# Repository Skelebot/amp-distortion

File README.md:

# Micro amp / distortion guitar pedal
Open-source micro amplifier guitar pedal with germanium diode distortion, heavily inspired by [MXR MicroAmp](https://www.jimdunlop.com/mxr-micro-amp/) and [MXR Distortion+](https://www.jimdunlop.com/mxr-distortion/).

## Features:
 - Clean and transparent volume boost with flat frequency response
 - Optional germanium diode signal clipping with a simple ON-ON switch (distortion)
 - True bypass using a 2PDT ON-ON switch
 - Completely un-colored sound, even with distortion on
 - Small board form factor (30mm x 55mm), most THT elements replaced with SMD
 - Smooth type distortion thanks to traditional germanium diodes
 - Wide distortion level range - from very soft to hard and saturated
 - Signal boost up to +34.7dB (54x voltage gain)
 - Designed to be powered by a 9V center-negative power adapter, but can be powered with up to 20V
 - Extremely low noise - uses a TL071 op-amp instead of more noisy TL061 (MicroAmp) or LM741 (Distortion+) amps
 - Can be easily fitted to smaller enclosures than both MXR MicroAmp and MXR Distortion+ (min. case size around 35 x 85mm)

## Customizing

 - **No distortion**: Do not install D2, D3 and SW1. Replace RV2 with a standard 10k resistor across its outer terminals
 - **Log pot instead of reverse-log**: Note that the middle pad of RV1 is not traced, so you can connect a standard logarithmic potentiometer backwards. Please note that when using a non-reverse-log potentiometer backwards, gain control will be reversed - the knob will have to be turned counter-clockwise to increase gain.
 - **On/Off LED**: The pedal does not have an on/off LED, which allows it to have true bypass with a 2PDT switch instead of a more expensive 3PDT switch. If you have a 3PDT switch, connect a LED+resistor to the leftover 3 terminals of the switch. Refer to [this image](https://mike-bland.com/images/3pdt-wiring.png) for a wiring diagram.
 - **Silicon diodes**: You can use standard silicon diodes (f.e. 1N4148) instead of germanium ones, but keep in mind that they usually have a much higher forward voltage - because of insufficient gain the pedal may not be able to create as much distortion, or may distort the sound only when the gain potentiometer is set to maximum.
 - **Different diodes**: Keep an eye on the diodes' forward voltage - it should be between 0.1 and 0.5V (±0.05V). The lower it is, the more distortion you will get. The pedal was tested with DOG35 and AAZ15 germanium diodes (Vf = 0.46V and 0.21 respectively) - distortion from the former was much less noticeable.

## BOM

|Ref     |Quantity|Value            |Description                                   |
|--------|--------|-----------------|----------------------------------------------|
|C1      |1       |1uF              |SMD Capacitor, package 0603 (1608 metric)     |
|C2, C4  |2       |47pF             |SMD Capacitor, package 0603 (1608 metric)     |
|C3      |1       |100nF            |SMD Capacitor, package 0603 (1608 metric)     |
|C5      |1       |10uF             |SMD Capacitor, package 0603 (1608 metric)     |
|D1      |1       |minimum 30V      |12.70mm THT Schottky diode                    |
|D2, D3  |2       |Vf = 0.1V to 0.5V|THT germanium diode                           |
|J1      |1       |-                |6.35mm THT audio jack (mono or stereo)        |
|J2      |1       |-                |DC Barrel jack                                |
|J3      |1       |-                |6.35mm THT audio jack (mono or stereo)        |
|R1      |1       |22M              |THT resistor                                  |
|R2      |1       |2.7K             |SMD resistor, package 0805 (2012 metric)      |
|R3, R4  |2       |100K             |SMD resistor, package 0805 (2012 metric)      |
|R5      |1       |10M              |THT resistor                                  |
|R6      |1       |1K               |SMD resistor, package 0805 (2012 metric)      |
|R7      |1       |150K             |SMD resistor, package 0805 (2012 metric)      |
|R8      |1       |470              |SMD resistor, package 0805 (2012 metric)      |
|RV1     |1       |500K             |Reverse-logarithmic 500K potentiometer (C500K)|
|RV2     |1       |10K              |Linear 10K potentiometer (B10K)               |
|SW1     |1       |-                |SPST ON-ON switch                             |
|U1      |1       |TL071            |TL071 op-amp, SO8 Package                     |
|-       |1       |-                |DPDT ON-ON foot switch (not on schematic)     |

## Making one yourself:

The board is single-sided and designed with loose tolerances between pads/traces for easy home-etching. I did not pay attention to the silkscreen, so if you want one fabricated remember to generate gerber files without it. Order boards without plated holes.
There are 5 bridges to be made on the board:
 - Between two holes over R8
 - Between two holes over R6
 - Between two closest terminals of R6 and C3
 - Between the center (negative) terminal of the DC jack and the copper pad left of D2/D3 (on the bottom of the board) 
 - Between the negative terminal of the DC jack and the closer ends of R4/C1
Refer to the brd file for a better view.
RV1, RV2 and the switches are soldered to the board with cables (not directly) so they can be mounted to the case independently.
The DPDT switch connections are described on the schematic (pad symbols are positioned as if you were looking on the bottom of the switch)
For the case, you can buy a universal enclosure of your choosing (make sure the board fits) and drill holes in it yourself, or print case.stl on a 3D printer.

#### *Made exclusively with open source tools*

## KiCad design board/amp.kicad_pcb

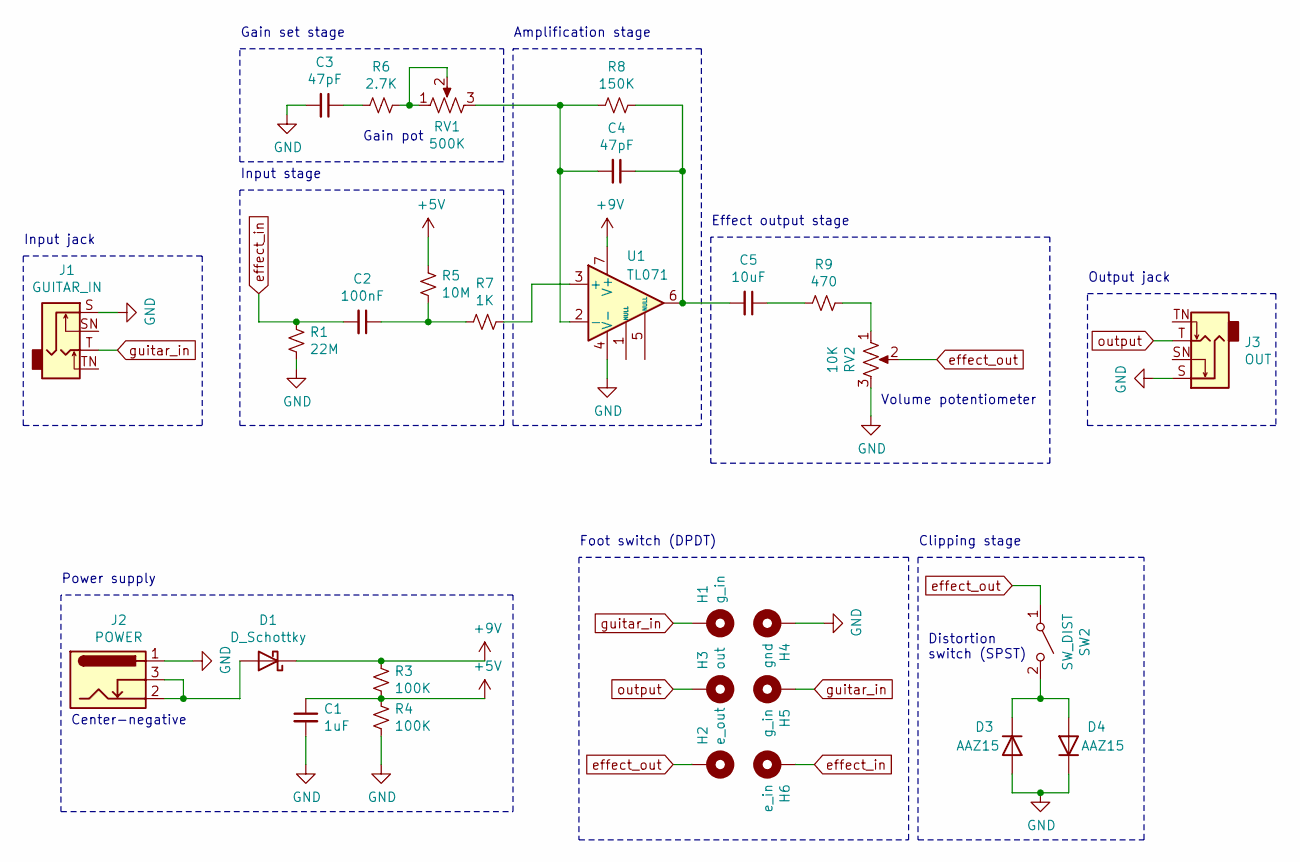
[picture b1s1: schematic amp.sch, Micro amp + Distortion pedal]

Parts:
C1: 1uF; C_0603_1608Metric
C2: 100nF; C_0603_1608Metric
C3, C4: 47pF; C_0603_1608Metric
C5: 10uF; C_0603_1608Metric
D1: D_Schottky; D_DO-15_P12.70mm_Horizontal
D3, D4: AAZ15; D_DO-35_SOD27_P12.70mm_Horizontal
H1, H5: g_in; TestPoint_Pad_D2.0mm
H2: e_out; TestPoint_Pad_D2.0mm
H3: out; TestPoint_Pad_D2.0mm
H4: gnd; TestPoint_Pad_D2.0mm
H6: e_in; TestPoint_Pad_D2.0mm
J1: GUITAR_IN; Jack_6.35mm_Neutrik_NRJ6HM-1-AU_Horizontal
J2: POWER; BarrelJack_Horizontal
J3: OUT; Jack_6.35mm_Neutrik_NRJ6HM-1-AU_Horizontal
R1: 22M; R_Axial_DIN0411_L9.9mm_D3.6mm_P12.70mm_Horizontal
R3, R4: 100K; R_0805_2012Metric_Pad1.15x1.40mm_HandSolder
R5: 10M; R_Axial_DIN0207_L6.3mm_D2.5mm_P7.62mm_Horizontal
R6: 2.7K; R_0805_2012Metric_Pad1.15x1.40mm_HandSolder
R7: 1K; R_0805_2012Metric_Pad1.15x1.40mm_HandSolder
R8: 150K; R_0805_2012Metric_Pad1.15x1.40mm_HandSolder
R9: 470; R_0805_2012Metric_Pad1.15x1.40mm_HandSolder
RV1: 500K; PinSocket_1x03_P2.54mm_Vertical
RV2: 10K; PinSocket_1x03_P2.54mm_Vertical
SW2: SW_DIST; PinSocket_1x02_P2.54mm_Vertical
U1: TL071; SO-8_5.3x6.2mm_P1.27mm

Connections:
+5V: C1.1, R3.2, R4.1, R5.1
+9V: D1.1 (K), R3.1, U1.7 (V+)
GND: C1.2, C3.2, D3.2 (A), D4.1 (K), H4.1, J1.S, J2.1, J3.S, R1.2, R4.2, RV2.3, U1.4 (V-)
unnamed: C2.1, R5.2, R7.2
unnamed: C3.1, R6.2
unnamed: C4.1, C5.2, R8.1, U1.6
unnamed: C4.2, R8.2, RV1.3, U1.2 (-)
unnamed: C5.1, R9.2
unnamed: D1.2 (A), J2.2, J2.3
unnamed: D3.1 (K), D4.2 (A), SW2.2 (B)
unnamed: R6.1, RV1.1, RV1.2
unnamed: R7.1, U1.3 (+)
unnamed: R9.1, RV2.1
effect_in: C2.2, H6.1, R1.1
effect_out: H2.1, RV2.2, SW2.1 (A)
guitar_in: H1.1, H5.1, J1.T
output: H3.1, J3.T

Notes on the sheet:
Clipping stage
Volume potentiometer
Gain pot
Power supply
Effect output stage
Input stage
Amplification stage
Gain set stage
Foot switch (DPDT)
Distortion switch (SPST)
Input jack
Output jack
Center-negative

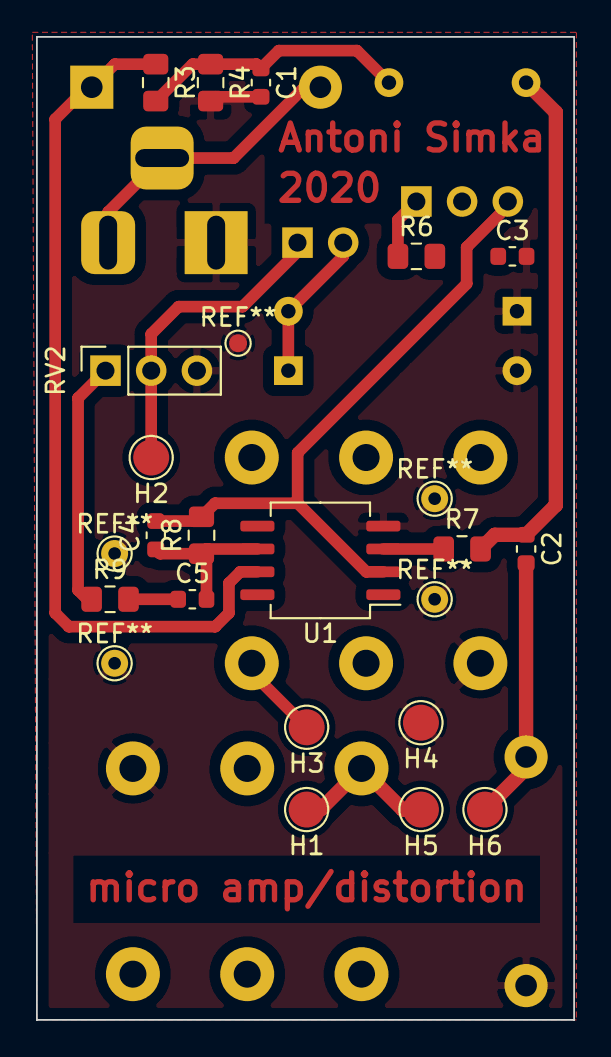
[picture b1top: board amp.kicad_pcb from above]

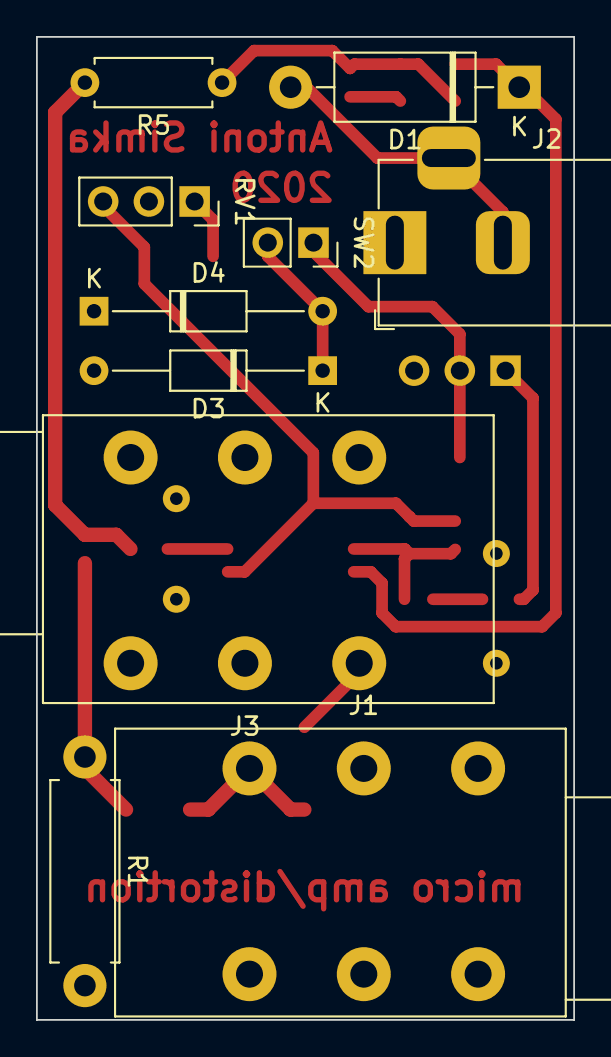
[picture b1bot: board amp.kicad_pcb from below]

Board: 2 copper layers, 29.8 x 54.6 mm, 29 parts (10 on the bottom side), 17 nets.

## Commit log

2020-11-07 Add schematic and board files rev v2
2020-11-07 Write README
2020-11-07 Add case 3D model
2020-11-07 Add BOM CSV
2020-11-08 Fix board, README corrections
    Reverse power jack polarity (make it center-negative), fix typos and
    other mistakes in README
